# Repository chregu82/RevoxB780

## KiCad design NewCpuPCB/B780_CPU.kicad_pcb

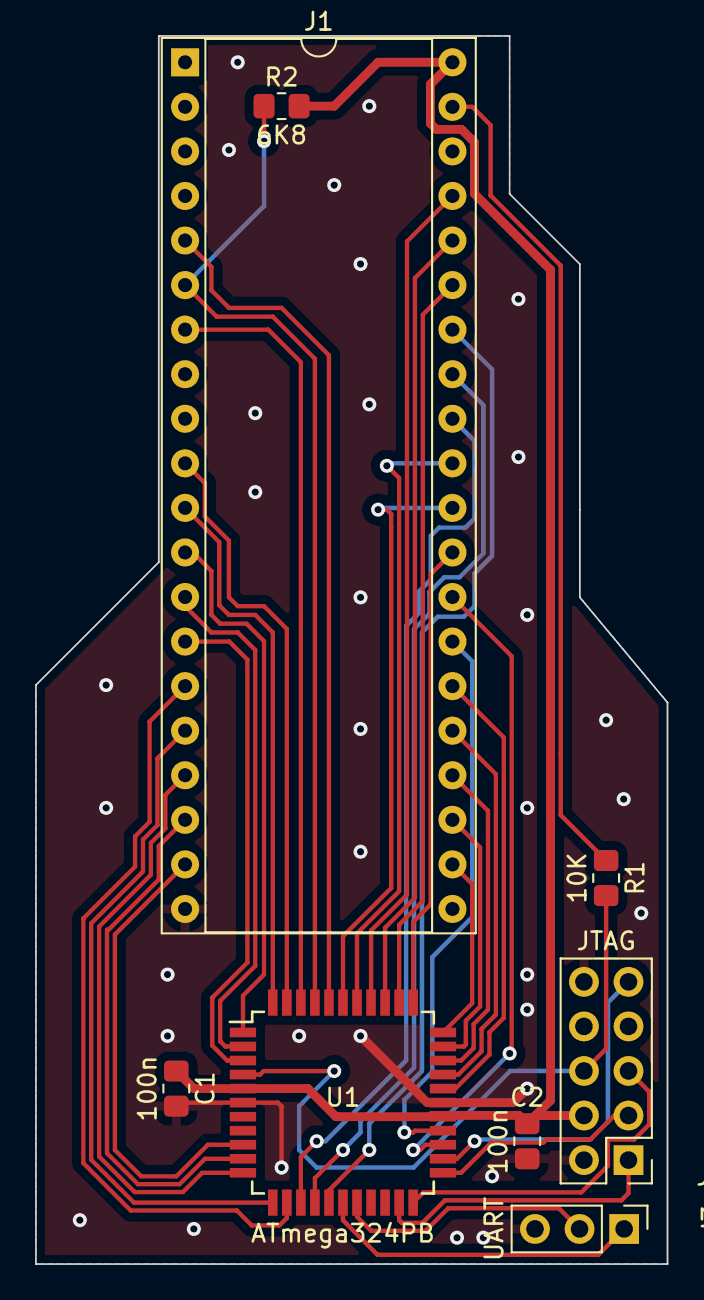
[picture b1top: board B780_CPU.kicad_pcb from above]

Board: 2 copper layers, 36.0 x 70.0 mm, 8 parts (0 on the bottom side), 39 nets.

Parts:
C1, C2: 100n; R_0805_2012Metric_Pad1.20x1.40mm_HandSolder
J1: MK3875; DIP-40_W15.24mm_Socket
J2: JTAG; PinHeader_2x05_P2.54mm_Vertical
J3: UART; PinHeader_1x03_P2.54mm_Vertical
R1: 10K; R_0805_2012Metric_Pad1.20x1.40mm_HandSolder
R2: 6K8; R_0805_2012Metric_Pad1.20x1.40mm_HandSolder
U1: ATmega324PB; TQFP-44_10x10mm_P0.8mm

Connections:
GND: C1.2, C2.2, J1.20, J2.2 (GND), J2.10 (GND), J3.3, U1.6 (GND), U1.28 (GND)
unnamed: J1.39, R1.1
unnamed: J3.1, U1.17 (PE2)
unnamed: J3.2, U1.18 (PE3)
P0.2_ST: J1.5, U1.40 (PB0)
P0.3_DON: J1.6, R2.1, U1.41 (PB1)
P0.4_NF1: J1.19, U1.9 (PD0)
P0.5_NF2: J1.18, U1.10 (PD1)
P0.6_NF3: J1.17, U1.11 (PD2)
P0.7_NF4: J1.16, U1.12 (PD3)
P1.0_A: J1.37, U1.37 (PA0)
P1.1_B: J1.36, U1.36 (PA1)
P1.2_C: J1.35, U1.35 (PA2)
P1.3_S: J1.34, U1.16 (PD7)
P1.5_NF6: J1.23, U1.32 (PA5)
P1.6_NF7: J1.24, U1.31 (PA6)
P1.7_NF5: J1.22, U1.33 (PA4)
P1.7_NF8: J1.25, U1.30 (PA7)
P4.2_DLEN5: J1.10, U1.43 (PB3)
P4.3_DLEN4: J1.11, U1.44 (PB4)
P4.4_DLEN3: J1.12, U1.1 (PB5)
P4.5_DLEN2: J1.13, U1.2 (PB6)
P4.6_DLEN1: J1.14, U1.3 (PB7)
P4.7_DATA: J1.15, U1.13 (PD4)
P5.0_PH: J1.33, U1.15 (PD6)
P5.1_PONLR: J1.32, U1.14 (PD5)
P5.2_Z: J1.31, U1.38 (PE5)
P5.3_Mul6: J1.30, U1.39 (PE6)
P5.4_Mul7: J1.29, U1.34 (PA3)
P5.5_Mul8: J1.28, U1.25 (PC6)
P5.6_Mul9: J1.27, U1.26 (PC7)
P5.7_Mul10: J1.26, U1.29 (PE4/AREF)
RESET: J2.6 (~SRST), R1.2, U1.4 (~RESET)
STROBE: J1.7, U1.42 (PB2)
TCK: J2.1 (TCK), U1.21 (PC2)
TDI: J2.9 (TDI), U1.24 (PC5)
TDO: J2.3 (TDO), U1.23 (PC4)
TMS: J2.5 (TMS), U1.22 (PC3)
VCC: C1.1, C2.1, J1.40, J2.4 (VREF), R2.2, U1.5 (VCC), U1.27 (AVCC)

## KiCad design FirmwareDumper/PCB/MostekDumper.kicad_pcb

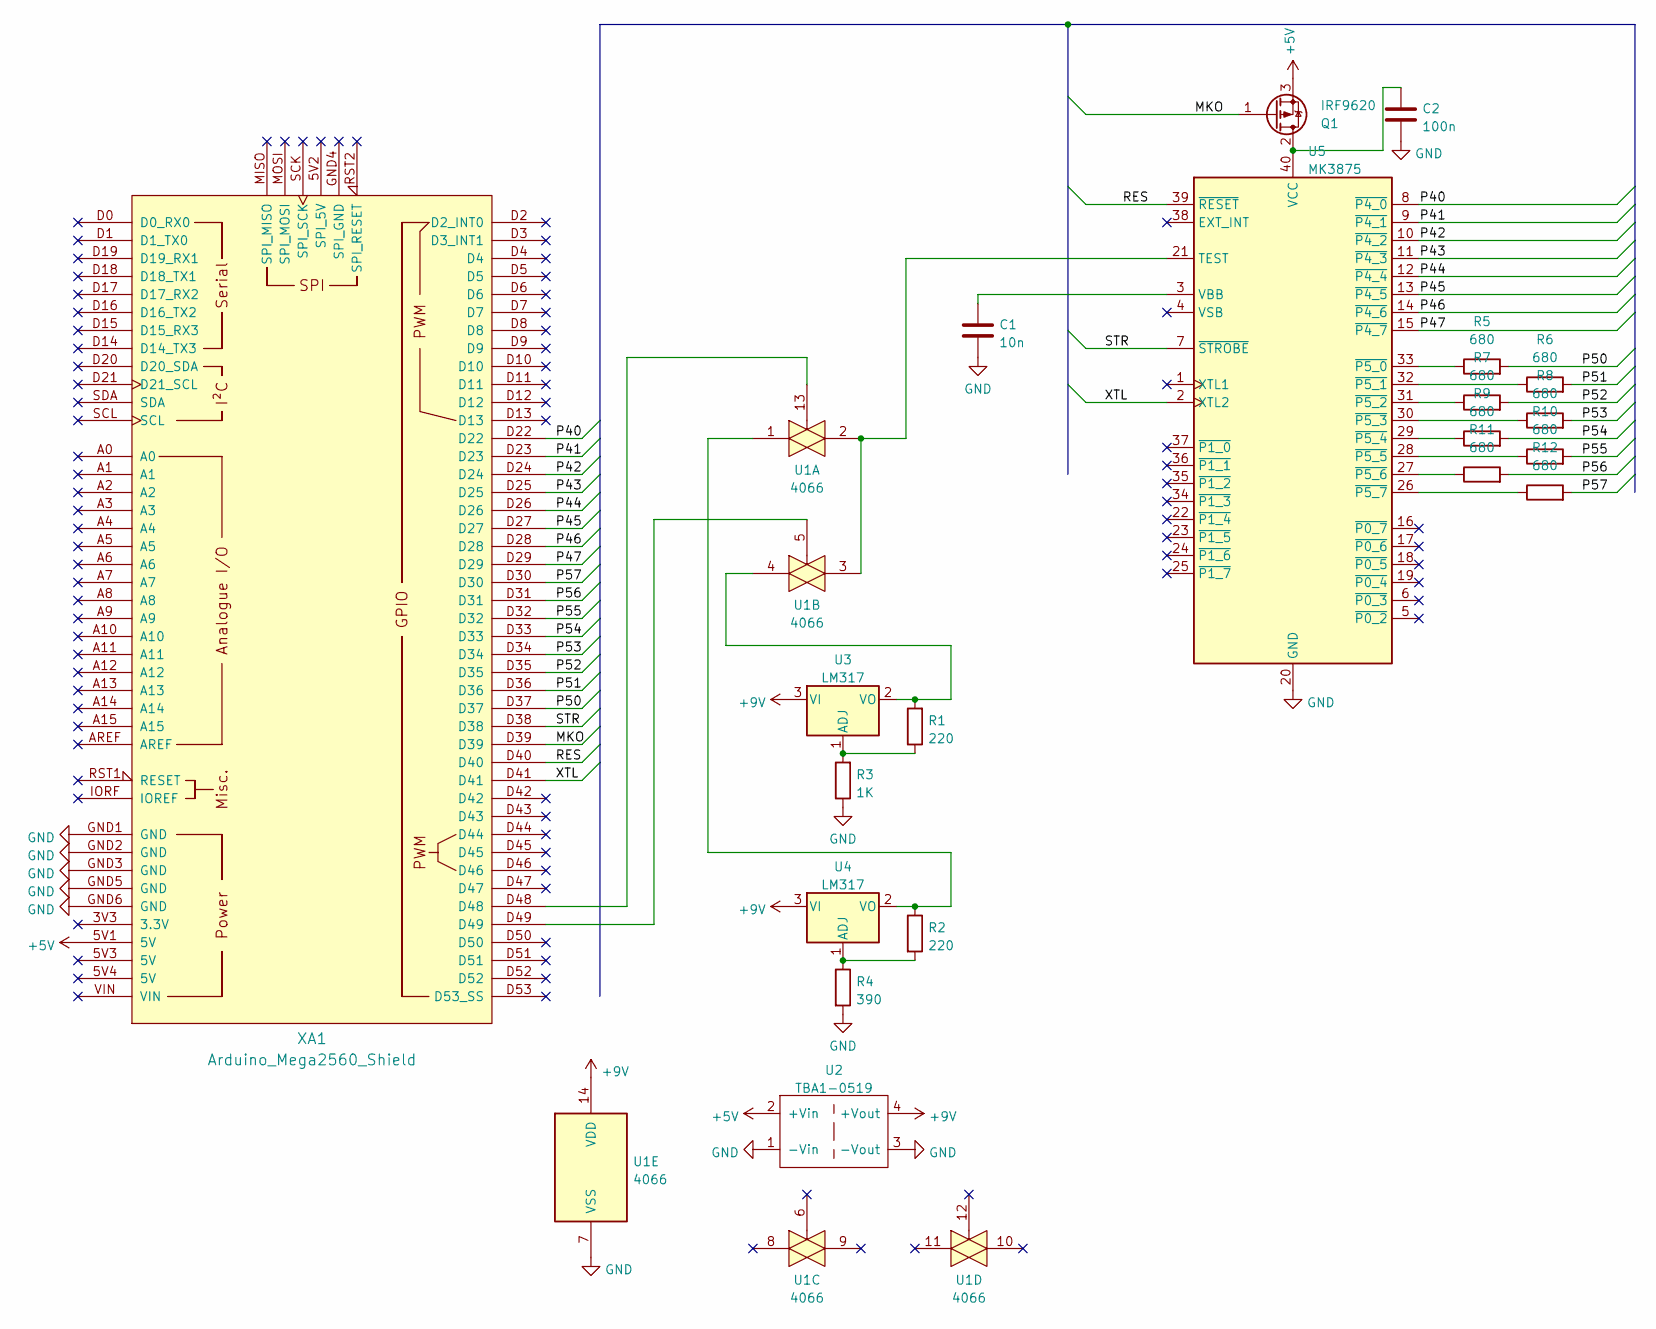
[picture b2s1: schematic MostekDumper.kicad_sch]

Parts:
C1: 10n; C_Disc_D3.0mm_W1.6mm_P2.50mm
C2: 100n; C_Disc_D4.3mm_W1.9mm_P5.00mm
Q1: IRF9620; TO-220-3_Vertical
R1, R2: 220; R_Axial_DIN0207_L6.3mm_D2.5mm_P10.16mm_Horizontal
R3: 1K; R_Axial_DIN0207_L6.3mm_D2.5mm_P10.16mm_Horizontal
R4: 390; R_Axial_DIN0207_L6.3mm_D2.5mm_P10.16mm_Horizontal
R5, R6, R7, R8, R9, R10, R11, R12: 680; R_Axial_DIN0207_L6.3mm_D2.5mm_P10.16mm_Horizontal
U1: 4066; DIP-14_W7.62mm_Socket
U2: TBA1-0519; TEA1-0505
U3, U4: LM317; TO-92_Inline
U5: MK3875; DIP-40_W15.24mm_Socket
XA1: Arduino_Mega2560_Shield

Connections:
+5V: Q1.3 (S), U2.2 (+Vin), XA1.5V1 (5V)
+9V: U1.14 (VDD), U2.4 (+Vout), U3.3 (VI), U4.3 (VI)
/MKO: Q1.1 (G), XA1.D39
/P40: U5.8 (~P4_0), XA1.D22
/P41: U5.9 (~P4_1), XA1.D23
/P42: U5.10 (~P4_2), XA1.D24
/P43: U5.11 (~P4_3), XA1.D25
/P44: U5.12 (~P4_4), XA1.D26
/P45: U5.13 (~P4_5), XA1.D27
/P46: U5.14 (~P4_6), XA1.D28
/P47: U5.15 (~P4_7), XA1.D29
/P50: R5.2, XA1.D37
/P51: R6.2, XA1.D36
/P52: R7.2, XA1.D35
/P53: R8.2, XA1.D34
/P54: R9.2, XA1.D33
/P55: R10.2, XA1.D32
/P56: R11.2, XA1.D31
/P57: R12.2, XA1.D30
/RES: U5.39 (~RESET), XA1.D40
/STR: U5.7 (~STROBE), XA1.D38
/XTL: U5.2 (XTL2), XA1.D41
GND: C1.2, C2.2, R3.1, R4.2, U1.7 (VSS), U2.1 (-Vin), U2.3 (-Vout), U5.20 (GND), XA1.GND1 (GND), XA1.GND2 (GND), XA1.GND3 (GND), XA1.GND5 (GND), XA1.GND6 (GND)
unnamed: C1.1, U5.3 (VBB)
unnamed: R1.1, R3.2, U3.1 (ADJ)
unnamed: R1.2, U1.4, U3.2 (VO)
unnamed: R2.1, U1.1, U4.2 (VO)
unnamed: R2.2, R4.1, U4.1 (ADJ)
unnamed: R5.1, U5.33 (~P5_0)
unnamed: R6.1, U5.32 (~P5_1)
unnamed: R7.1, U5.31 (~P5_2)
unnamed: R8.1, U5.30 (~P5_3)
unnamed: R9.1, U5.29 (~P5_4)
unnamed: R10.1, U5.28 (~P5_5)
unnamed: R11.1, U5.27 (~P5_6)
unnamed: R12.1, U5.26 (~P5_7)
unnamed: U1.2, U1.3, U5.21 (TEST)
unnamed: U1.5, XA1.D49
unnamed: U1.13, XA1.D48
unnamed: C2.1, Q1.2 (D), U5.40 (VCC)

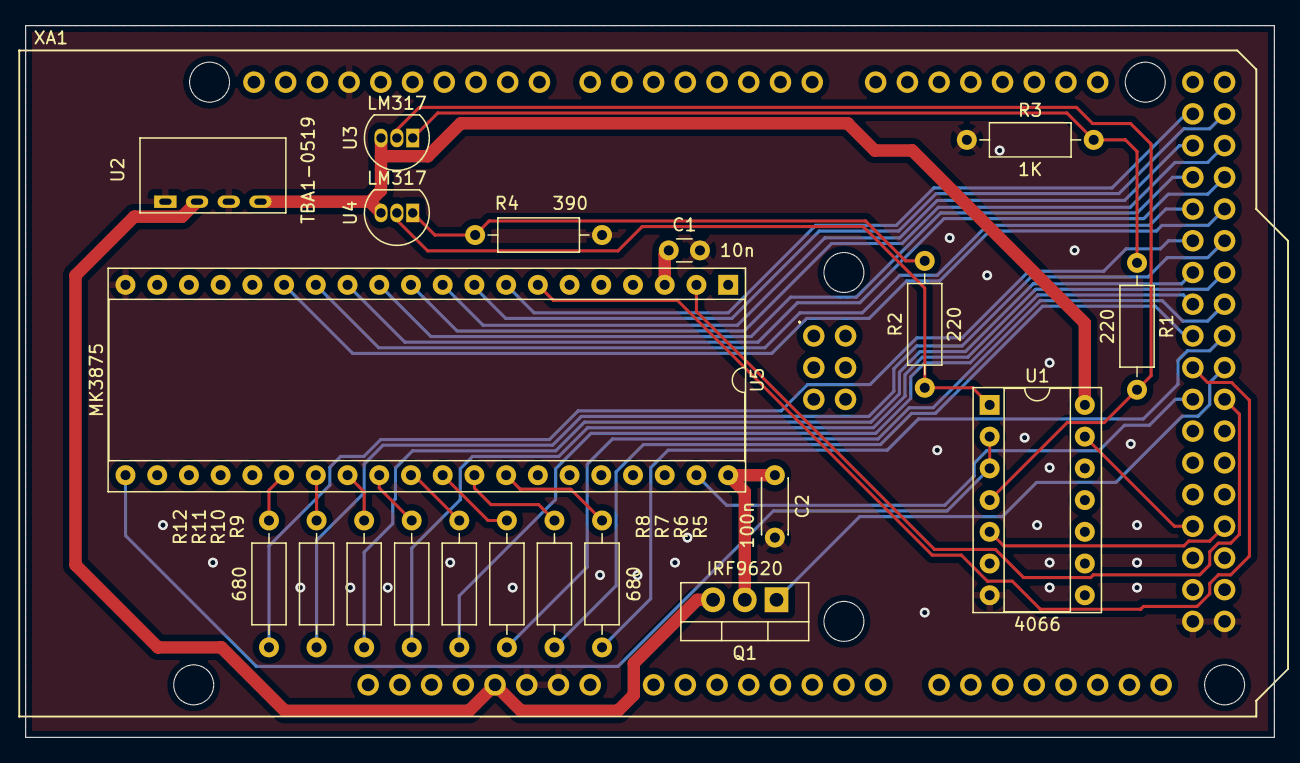
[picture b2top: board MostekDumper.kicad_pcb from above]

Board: 2 copper layers, 100.0 x 57.0 mm, 21 parts (0 on the bottom side), 40 nets.

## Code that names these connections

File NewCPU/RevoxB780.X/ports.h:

/* 
 * File:   ports.h
 * Author: lehne
 *
 * Created on 26. Februar 2024, 20:51
 */

#ifndef PORTS_H
#define	PORTS_H

#ifdef	__cplusplus
extern "C" {
#endif

#define F_CPU 8000000
#include <util/delay.h>
#include <avr/io.h>

// Port A
#define OUT_PA0_A PA0
#define OUT_PA1_B PA1
#define OUT_PA2_C PA2
#define IN_PA3_Mul7 PA3
#define OUT_PA4_NF5 PA4
#define OUT_PA5_NF6 PA5
#define OUT_PA6_NF7 PA6
#define OUT_PA7_NF8 PA7
    
//Port B
#define OUT_PB0_ST PB0
#define OUT_PB1_DON PB1
#define OUT_PB2_STROBE PB2
#define OUT_PB3_DLEN5 PB3
#define OUT_PB4_DLEN4_OUTMUL PB4
#define OUT_PB5_DLEN3_TUNER PB5
#define OUT_PB6_DLEN2_DISP_RIGHT PB6
#define OUT_PB7_DLEN1_DISP_LEFT PB7
    
//Port C
#define IN_PC6_Mul8 PC6
#define IN_PC7_Mul9 PC7
    
//Port D
#define OUT_PD0_NF1 PD0
#define OUT_PD1_NF2 PD1
#define OUT_PD2_NF3 PD2
#define OUT_PD3_NF4 PD3
#define OUT_PD4_DATA PD4
#define OUT_PD5_PONLR PD5
#define OUT_PD6_PH PD6
#define OUT_PD7_S PD7
    
//Port E
#define IN_PE4_Mul10 PE4
#define IN_PE5_Z PE5
#define IN_PE6_Mul6 PE6
    
// Keys
#define NBR_OF_PROG_KEYS 10
    
typedef struct InputsType
{
    unsigned char H;    // Overtemperature      -> done
    unsigned char DDE;  // Dolby Deemphasis     -> obsolete
    unsigned char HIBL; // High blend           
    unsigned char STME; // Store Memory
    unsigned char KS8;  // Key 8
    unsigned char RECOFF;   // Record output off
    unsigned char NR;   // Noise reduction
    unsigned char P;    // Pilot Present
    unsigned char CHTM; // Change Tuning Mode
    unsigned char KS7;  // Key 7
    unsigned char RECSET;   // Set record output
    unsigned char NOD;  // No Dolby Insert
    unsigned char MONO; // FM Mono
    unsigned char LSNE; // New entry (Star key)
    unsigned char KS6;  // Key 6
    unsigned char TA2;  // Tape 2 (5)
    unsigned char FL;   // Frequency too low (if signal = 0)
    unsigned char MOFF; // Muting off
    unsigned char DOWN; // Down key
    unsigned char KS5;  // Key 5
    unsigned char TA1;  // Tape 1 (4)
    unsigned char FH;   // Frequency too high (if signal = 1)
    unsigned char THSTA;    // Threshold Station
    unsigned char UP;   // Up key
    unsigned char KS4;  // Key 4
    unsigned char AUX;  // Aux (3)
    unsigned char TSPB; // Speaker B
    unsigned char STLY; // Stereo only
    unsigned char D75us;    // Deemphasis 75us
    unsigned char KS3;  // Key 3
    unsigned char PHO;  // Phono (2)
    unsigned char TSPA; // Speaker A
    unsigned char THSTE;    // Threshold Stereo
    unsigned char KS0;  // Key 0
    unsigned char KS2;  // Key 2
    unsigned char TU;   // Tuner (1)
    unsigned char DC;   // DC at Amp
    unsigned char LOC;  // Synthesizer locked in
    unsigned char KS9;  // Key 9
    unsigned char KS1;  // Key 1
    unsigned char Z;    // Antenna
} InputsType;

typedef struct DisplayTuningRecordPlayType
{
    unsigned char LowerUpper;
    unsigned char TuningMode;
    unsigned char DolbyLed;
    unsigned char Record;
    unsigned char StereoLed;
    unsigned char Play;
    unsigned char Refresh;
} DisplayTuningRecordPlayType;
    
typedef enum MultiplexOutEnum
{
    Mul_Out_STFI,
    Mul_Out_MC,
    Mul_Out_25us,
    Mul_Out_75us,
    Mul_Out_WW,
    Mul_Out_SPB,
    Mul_Out_SPA,
    Mul_Out_MUT
} MultiplexOutEnum;

// Frequency low value
// Logic is inverse
static const unsigned char FreqLow[31] = {
    0b01010000, // 0
    0b11111001, // 1
    0b00110010, // 2
    0b10110000, // 3
    0b10011001, // 4
    0b10010100, // 5
    0b00000100, // 6
    0b11110001, // 7
    0b00010000, // 8
    0b10010000, // 9
    0b00010001, // A
    0b00011100, // B
    0b01010110, // C
    0b00111000, // d
    0b00010110, // E
    0b00010111, // F
    0b10010000, // G
    0b00011001, // H
    0b11111001, // I
    0b11111000, // J
    0b11111111, // K
    0b01011110, // L
    0b11111111, // M
    0b11111111, // N
    0b01010000, // O
    0b00010011, // P
    0b11111111, // Q
    0b11111111, // R
    0b10010100, // S
    0b00011110, // T
    0b01011000, // U
};

// Frequency high value
// Logic is inverse
static const unsigned char FreqHigh[31] = {
    0b00010000, // 0
    0b01010111, // 1
    0b01001000, // 2
    0b01000010, // 3
    0b00000111, // 4
    0b00100010, // 5
    0b00100000, // 6
    0b01010011, // 7
    0b00000000, // 8
    0b00000010, // 9
    0b00000001, // A
    0b00100100, // B
    0b00111000, // C
    0b01000100, // d
    0b00101000, // E
    0b00101001, // F
    0b00000010, // G
    0b00000101, // H
    0b01010111, // I
    0b01010110, // J
    0b11111111, // K
    0b00111100, // L
    0b11111111, // M
    0b11111111, // N
    0b00010000, // O
    0b00001001, // P
    0b11111111, // Q
    0b11111111, // R
    0b00100010, // S
    0b00101100, // T
    0b00010100, // U
};

// Tuning mode (memory slot)
// Logic is inverse
static const unsigned char TuningModeDisp[12] = {
    0b01111111, // off
    0b00111011, // 1
    0b00000110, // 2
    0b00100010, // 3
    0b00101001, // 4
    0b01100000, // 5
    0b01000000, // 6
    0b00110011, // 7
    0b00000000, // 8
    0b00100000, // 9
    0b00000001, // A
    0b01000101, // F
};

// Record Display
// Logic is inverse
static const unsigned char RecordPlayDisp[7] = {
    0b01111111, // off
    0b01110011, // 1
    0b00001010, // 2
    0b00010010, // 3
    0b01110000, // 4
    0b00010100, // 5
    0b11011111, // _
};

void LoadOutputMultiplexer(MultiplexOutEnum outputNbr, unsigned char value);
void WriteToSAA(unsigned char pin, unsigned short data, unsigned char loadbit);
void DisplayFreq(unsigned char On, unsigned char dig1, unsigned char dig2, unsigned char dig3, unsigned char dig4, unsigned char dig5);
void DisplayTuningRecordPlay(DisplayTuningRecordPlayType* p);

void ReadInputs(InputsType* Inputs);
void ReadInputsWithCheck(InputsType* Inputs1, InputsType* Inputs2);

unsigned char DetectKS_Keys(InputsType* pIn, unsigned char* pOld, unsigned char* pEdge);

#ifdef	__cplusplus
}
#endif

#endif	/* PORTS_H */

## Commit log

2024-01-23 Firmware dumper software, PCB, decompiler and datasheets
2024-01-28 Changed to c
2024-02-22 New CPU board as direct replacement
2024-02-25 Atmega project
2024-03-03 Init outputs
2024-03-05 Display working
2024-03-05 Frequency display working
2024-03-07 Reading inputs
2024-03-08 Set Play
2024-03-09 Input selection working like original
2024-03-10 Set Record and play working
2024-03-10 Improved record off
2024-03-10 Improved rec / play select
2024-03-10 Started with protection logic
2024-03-13 Protection working
2024-03-13 Improved protection
2024-03-14 Bugfix for play selection
2024-03-14 Set deemphasis
2024-03-15 Reverse engineering
2024-03-18 Ability to tune to a frequency
2024-03-19 EEPROM
2024-03-19 Redesign of right display
2024-03-21 Tuning mode / KS keys
2024-03-23 AutoTuning
    AutoTuning kind of working, built a TimeOnDelay Function, small bugfixes
2024-03-31 AutoTuning working
